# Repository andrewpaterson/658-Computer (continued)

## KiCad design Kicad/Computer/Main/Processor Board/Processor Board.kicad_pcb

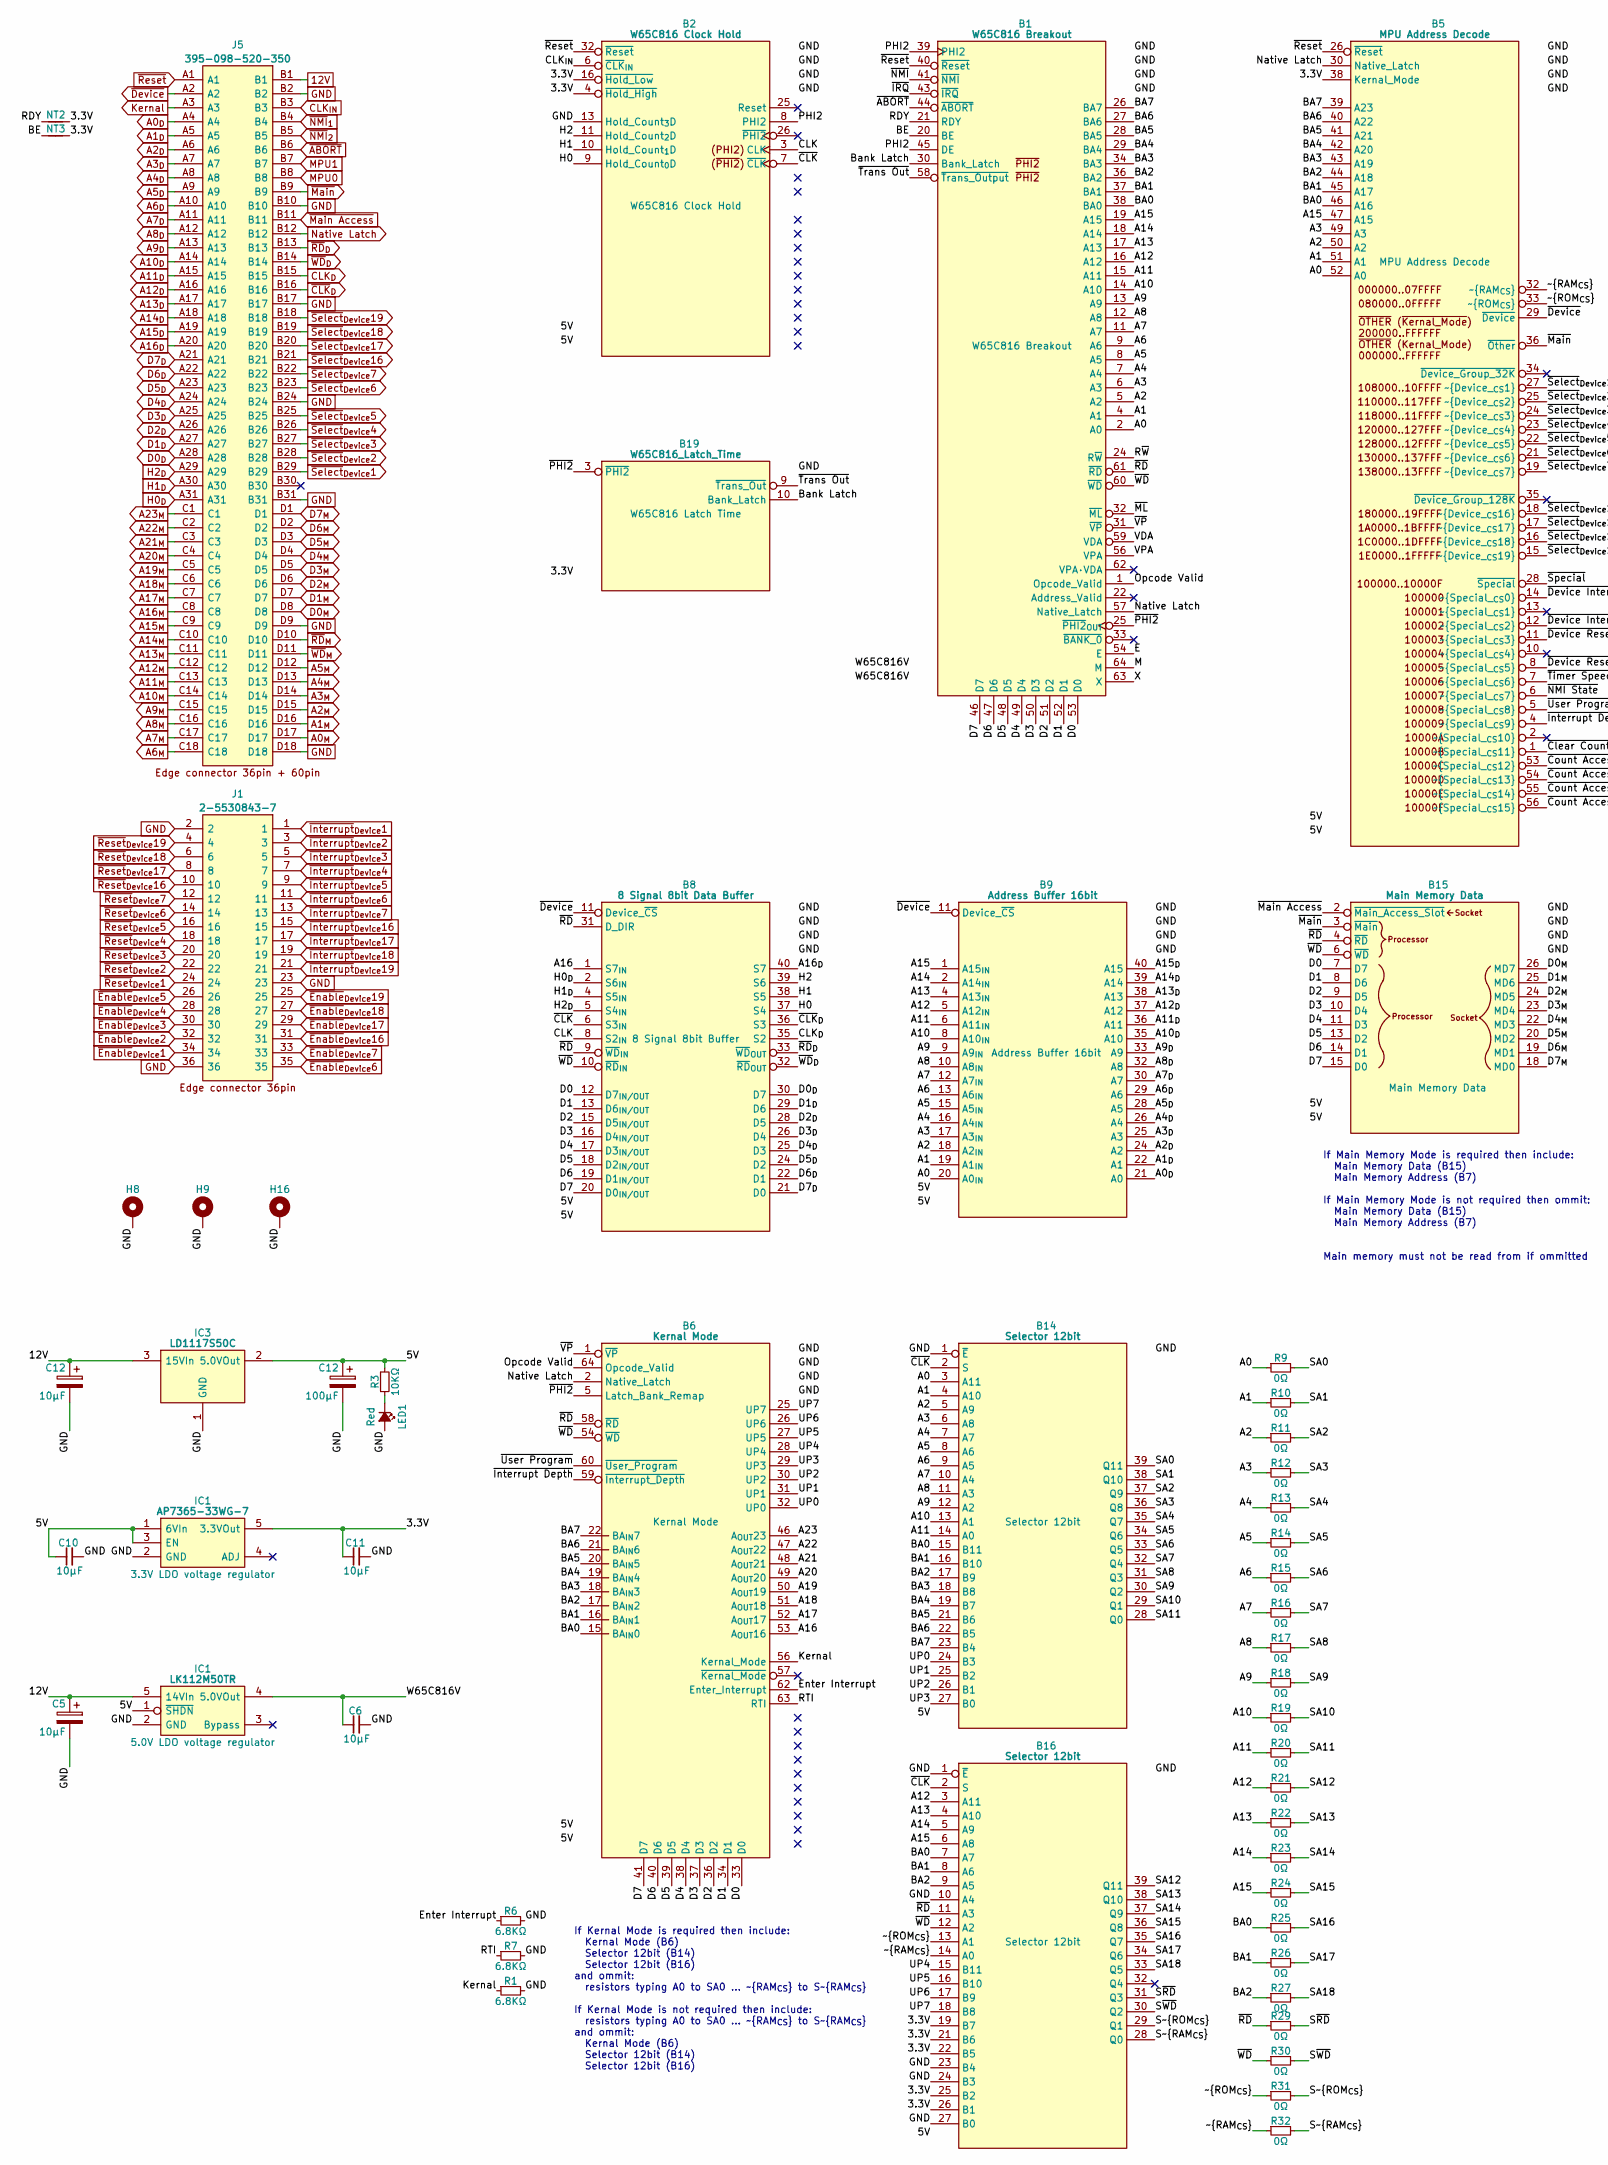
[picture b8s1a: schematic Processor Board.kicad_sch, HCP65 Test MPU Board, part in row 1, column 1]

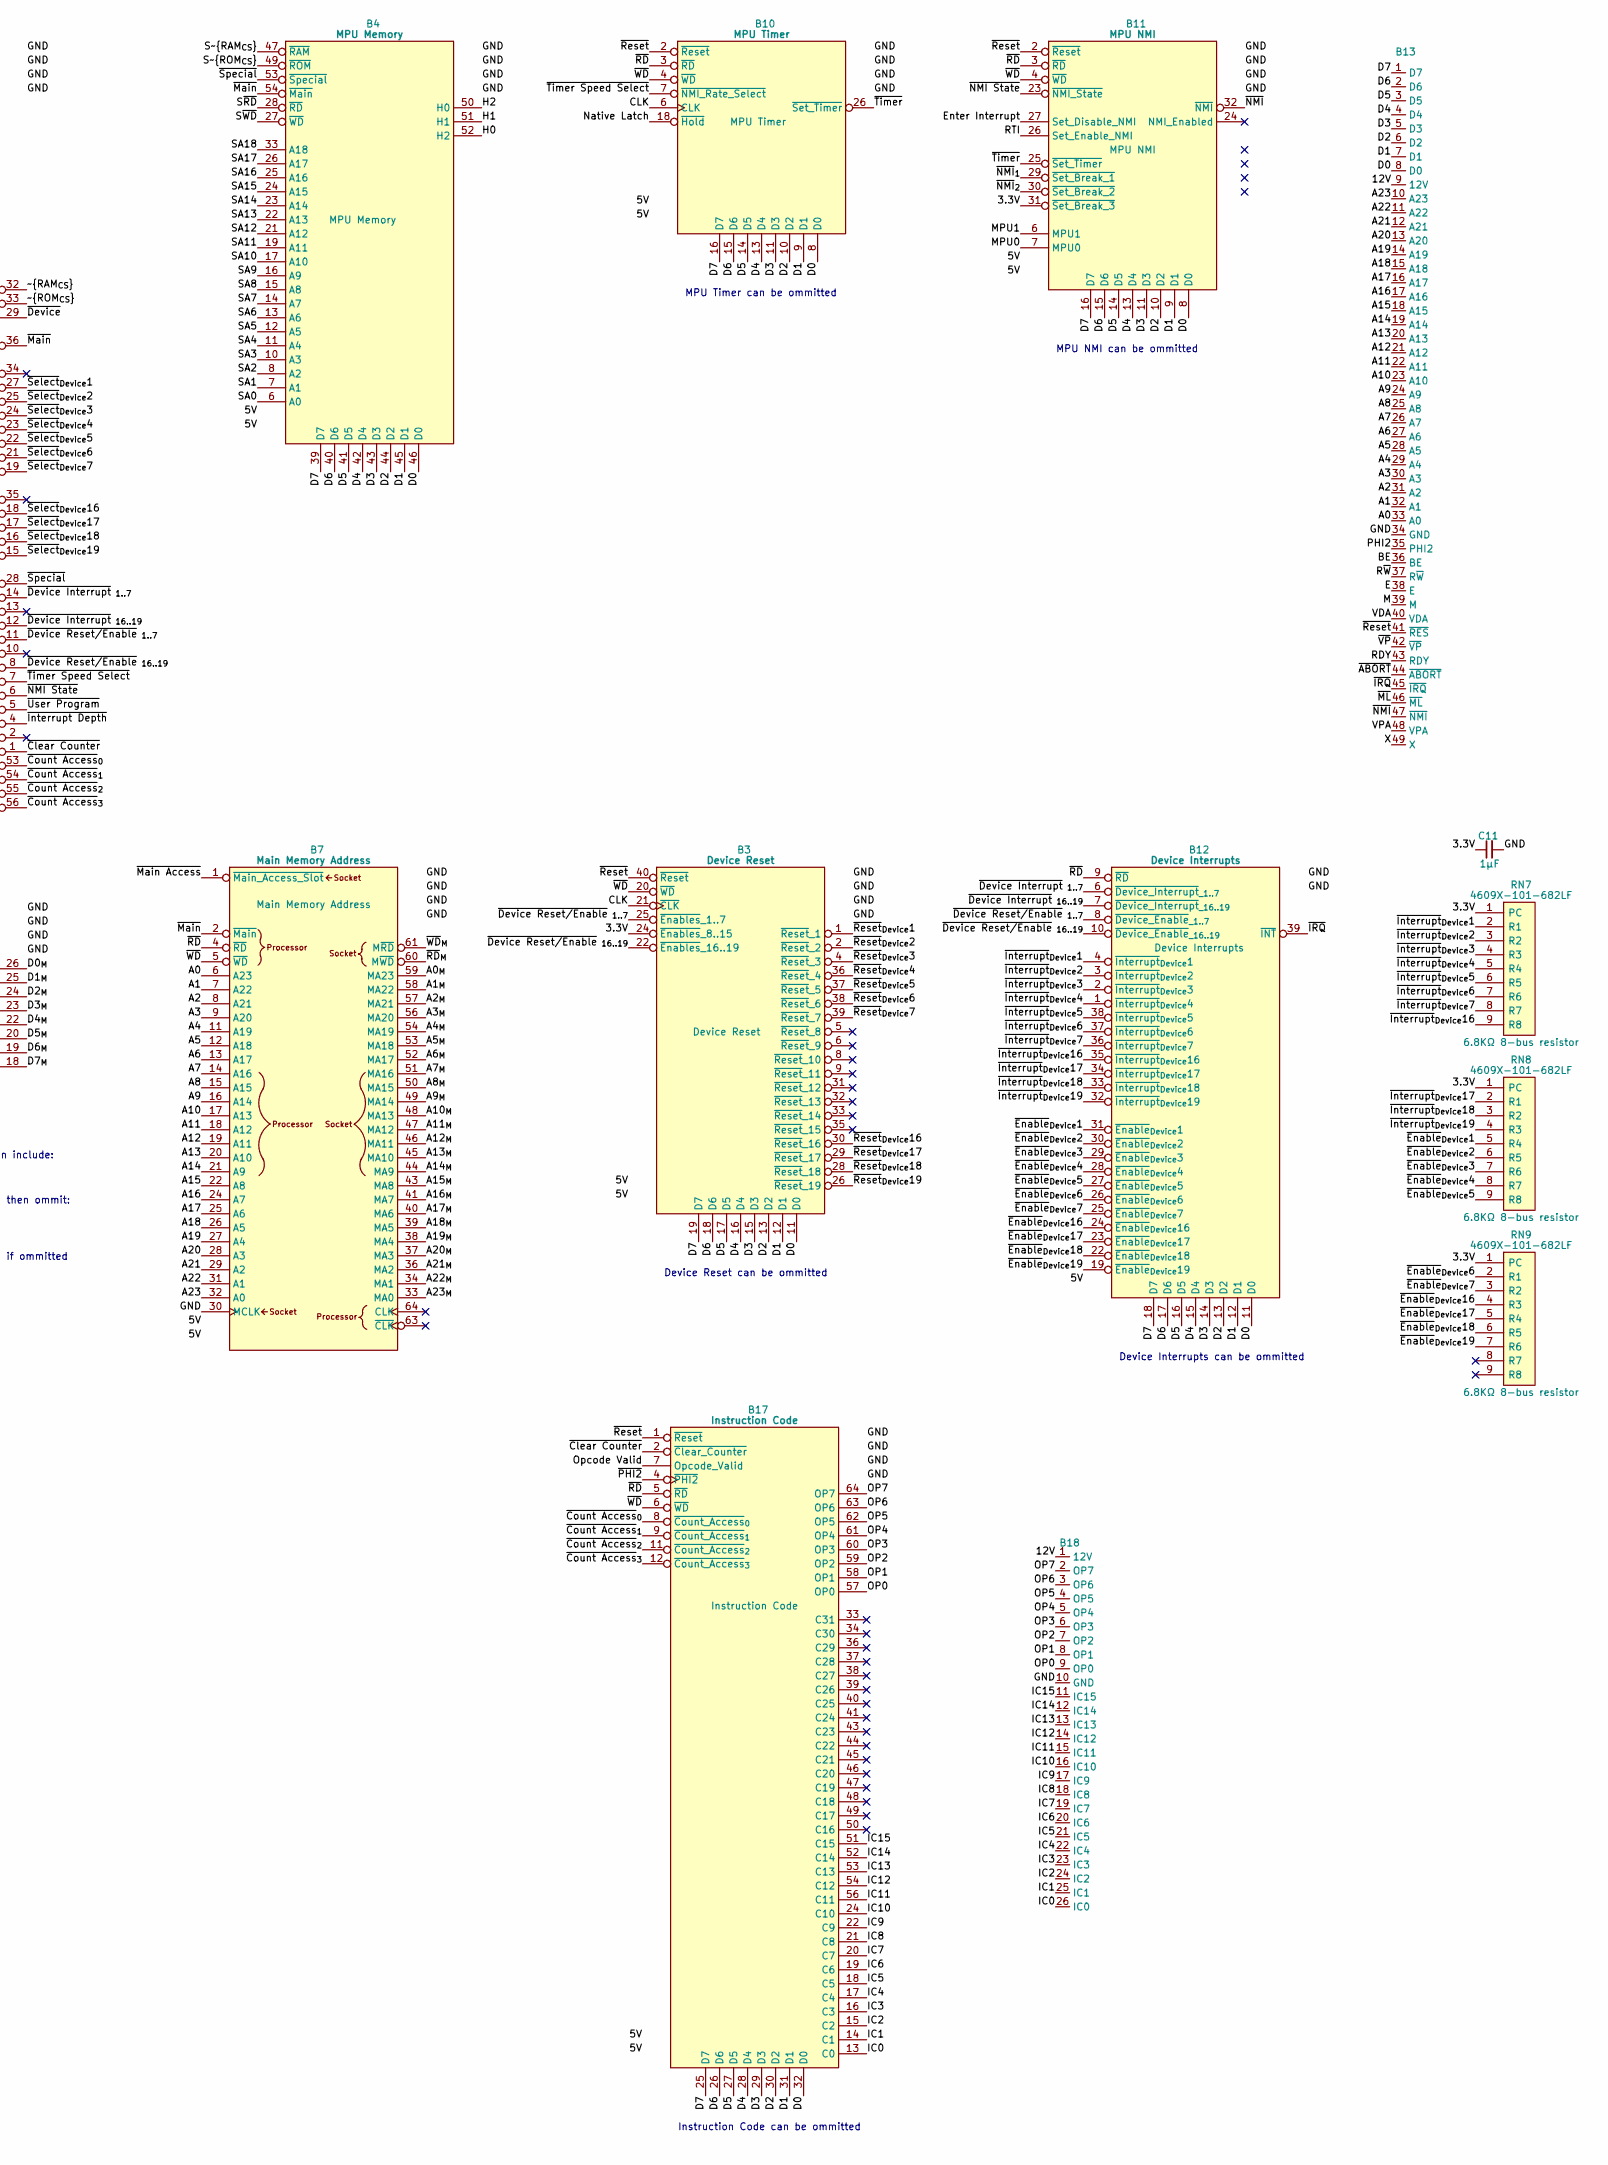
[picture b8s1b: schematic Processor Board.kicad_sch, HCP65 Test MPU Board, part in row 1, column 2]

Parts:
B1: W65C816 Breakout; HCP65_W65C816_Breakout
B2: W65C816 Clock Hold; HCP65_W65C816_Clock_Hold
B3: Device Reset; HCP65_Device_Reset
B4: MPU Memory; HCP65_MPU_Memory
B5: MPU Address Decode; HCP65_MPU_Address_Decode
B6: Kernal Mode; HCP65_Kernal_Mode
B7: Main Memory Address; HCP65_Main_Memory_Address
B8: 8 Signal 8bit Data Buffer; HCP65_Data_and_Signal_Buffer
B9: Address Buffer 16bit; HCP65_Address_Buffer_16bit
B10: MPU Timer; HCP65_MPU_Timer
B11: MPU NMI; HCP65_MPU_NMI
B12: Device Interrupts; HCP65_Device_Interrupts
B13: HCP65_W65C816_Debug_Display
B14, B16: Selector 12bit; HCP65_Selector_12bit
B15: Main Memory Data; HCP65_Main_Memory_Data
B17: Instruction Code; HCP65_Instruction_Code
B18: HCP65_W65C816_Debug_Instruction
B19: W65C816_Latch_Time; HCP65_W65C816_Latch_Time
C5: 10μF; CP_Radial_D4.0mm_P2.00mm
C6, C10: 10µF; C_0805
C11: 1μF; C_0805
C12: 100μF; CP_Radial_D4.0mm_P2.00mm
H8, H9, H16: MountingHole_Pad; HCP65_MountingHole_M3_
IC1: AP7365-33WG-7; SOT95P285X130-5N; Manufacturer_Part_Number AP7365-33WG-7; Mouser Part Number 621-AP7365-33WG-7
IC3: LD1117S50C; LD1117S33C; Manufacturer_Part_Number LD1117S50C
J1: 2-5530843-7; 36pin Edge Connector; Manufacturer_Part_Number 2-5530843-7; Mouser Part Number 571-2-5530843-7
J5: 395-098-520-350; 98pin Edge Connector; Manufacturer_Part_Number 395-098-520-350; Mouser Part Number 587-395-098-520-350
LED1: Red; LED_D5.0mm
NT2, NT3: NetTie; NetTie-2_SMD_Pad0.5mm
R1, R6, R7: 6.8KΩ; R_0805
R3: 10KΩ; R_0805
R9, R10, R11, R12, R13, R14, R15, R16, R17, R18, R19, R20, R21, R22, R23, R24, R25, R26, R27, R29, R30, R31, R32: 0Ω; R_0805
RN7, RN8, RN9: 4609X-101-682LF; 4609X; Manufacturer_Part_Number 4609X-101-682LF; Mouser Part Number 652-4609X-1LF-6.8K

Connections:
/A0: B1.2 (A0), B5.52 (A0), B7.6 (A23), B9.20 (A0_{IN}), B13.33 (A0), B14.3 (A11), R9.1
/A1: B1.4 (A1), B5.51 (A1), B7.7 (A22), B9.19 (A1_{IN}), B13.32 (A1), B14.4 (A10), R10.1
/A2: B1.5 (A2), B5.50 (A2), B7.8 (A21), B9.18 (A2_{IN}), B13.31 (A2), B14.5 (A9), R11.1
/A3: B1.6 (A3), B5.49 (A3), B7.9 (A20), B9.17 (A3_{IN}), B13.30 (A3), B14.6 (A8), R12.1
/A4: B1.7 (A4), B7.11 (A19), B9.16 (A4_{IN}), B13.29 (A4), B14.7 (A7), R13.1
/A5: B1.8 (A5), B7.12 (A18), B9.15 (A5_{IN}), B13.28 (A5), B14.8 (A6), R14.1
/A6: B1.9 (A6), B7.13 (A17), B9.13 (A6_{IN}), B13.27 (A6), B14.9 (A5), R15.1
/A7: B1.11 (A7), B7.14 (A16), B9.12 (A7_{IN}), B13.26 (A7), B14.10 (A4), R16.1
/A8: B1.12 (A8), B7.15 (A15), B9.10 (A8_{IN}), B13.25 (A8), B14.11 (A3), R17.1
/A9: B1.13 (A9), B7.16 (A14), B9.9 (A9_{IN}), B13.24 (A9), B14.12 (A2), R18.1
/A10: B1.14 (A10), B7.17 (A13), B9.8 (A10_{IN}), B13.23 (A10), B14.13 (A1), R19.1
/A11: B1.15 (A11), B7.18 (A12), B9.6 (A11_{IN}), B13.22 (A11), B14.14 (A0), R20.1
/A12: B1.16 (A12), B7.19 (A11), B9.5 (A12_{IN}), B13.21 (A12), B16.3 (A11), R21.1
/A13: B1.17 (A13), B7.20 (A10), B9.4 (A13_{IN}), B13.20 (A13), B16.4 (A10), R22.1
/A14: B1.18 (A14), B7.21 (A9), B9.2 (A14_{IN}), B13.19 (A14), B16.5 (A9), R23.1
/A15: B1.19 (A15), B5.47 (A15), B7.22 (A8), B9.1 (A15_{IN}), B13.18 (A15), B16.6 (A8), R24.1
/A16: B6.53 (A_{OUT}16), B7.24 (A7), B8.1 (S7_{IN}), B13.17 (A16)
/A17: B6.52 (A_{OUT}17), B7.25 (A6), B13.16 (A17)
/A18: B6.51 (A_{OUT}18), B7.26 (A5), B13.15 (A18)
/A19: B6.50 (A_{OUT}19), B7.27 (A4), B13.14 (A19)
/A20: B6.49 (A_{OUT}20), B7.28 (A3), B13.13 (A20)
/A21: B6.48 (A_{OUT}21), B7.29 (A2), B13.12 (A21)
/A22: B6.47 (A_{OUT}22), B7.31 (A1), B13.11 (A22)
/A23: B6.46 (A_{OUT}23), B7.32 (A0), B13.10 (A23)
/BA0: B1.38 (BA0), B5.46 (A16), B6.15 (BA_{IN}0), B14.15 (B11), B16.7 (A7), R25.1
/BA1: B1.37 (BA1), B5.45 (A17), B6.16 (BA_{IN}1), B14.16 (B10), B16.8 (A6), R26.1
/BA2: B1.36 (BA2), B5.44 (A18), B6.17 (BA_{IN}2), B14.17 (B9), B16.9 (A5), R27.1
/BA3: B1.34 (BA3), B5.43 (A19), B6.18 (BA_{IN}3), B14.18 (B8)
/BA4: B1.29 (BA4), B5.42 (A20), B6.19 (BA_{IN}4), B14.19 (B7)
/BA5: B1.28 (BA5), B5.41 (A21), B6.20 (BA_{IN}5), B14.21 (B6)
/BA6: B1.27 (BA6), B5.40 (A22), B6.21 (BA_{IN}6), B14.22 (B5)
/BA7: B1.26 (BA7), B5.39 (A23), B6.22 (BA_{IN}7), B14.23 (B4)
/BE: B1.20 (BE), B13.36 (BE), NT3.1
/Bank Latch: B1.30 (Bank_Latch), B19.10 (Bank_Latch)
/CLK: B2.3 (CLK), B3.21 (~CLK), B8.8 (S2_{IN}), B10.6 (CLK)
/D0: B1.53 (D0), B3.11 (D0), B4.46 (D0), B6.33 (D0), B8.12 (D7_{IN/OUT}), B10.8 (D0), B11.8 (D0), B12.11 (D0), B13.8 (D0), B15.7 (D7), B17.32 (D0)
/D1: B1.52 (D1), B3.12 (D1), B4.45 (D1), B6.34 (D1), B8.13 (D6_{IN/OUT}), B10.9 (D1), B11.9 (D1), B12.12 (D1), B13.7 (D1), B15.8 (D6), B17.31 (D1)
/D2: B1.51 (D2), B3.13 (D2), B4.44 (D2), B6.36 (D2), B8.15 (D5_{IN/OUT}), B10.10 (D2), B11.10 (D2), B12.13 (D2), B13.6 (D2), B15.9 (D5), B17.30 (D2)
/D3: B1.50 (D3), B3.15 (D3), B4.43 (D3), B6.37 (D3), B8.16 (D4_{IN/OUT}), B10.11 (D3), B11.11 (D3), B12.14 (D3), B13.5 (D3), B15.10 (D4), B17.29 (D3)
/D4: B1.49 (D4), B3.16 (D4), B4.42 (D4), B6.38 (D4), B8.17 (D3_{IN/OUT}), B10.13 (D4), B11.13 (D4), B12.15 (D4), B13.4 (D4), B15.11 (D3), B17.28 (D4)
/D5: B1.48 (D5), B3.17 (D5), B4.41 (D5), B6.39 (D5), B8.18 (D2_{IN/OUT}), B10.14 (D5), B11.14 (D5), B12.16 (D5), B13.3 (D5), B15.13 (D2), B17.27 (D5)
/D6: B1.47 (D6), B3.18 (D6), B4.40 (D6), B6.40 (D6), B8.19 (D1_{IN/OUT}), B10.15 (D6), B11.15 (D6), B12.17 (D6), B13.2 (D6), B15.14 (D1), B17.26 (D6)
/D7: B1.46 (D7), B3.19 (D7), B4.39 (D7), B6.41 (D7), B8.20 (D0_{IN/OUT}), B10.16 (D7), B11.16 (D7), B12.18 (D7), B13.1 (D7), B15.15 (D0), B17.25 (D7)
/E: B1.54 (E), B13.38 (E)
/Enter Interrupt: B6.62 (Enter_Interrupt), B11.27 (Set_Disable_NMI), R6.1
/H0: B2.9 (Hold_Count_{0}D), B4.52 (H2), B8.37 (S4)
/H1: B2.10 (Hold_Count_{1}D), B4.51 (H1), B8.38 (S5)
/H2: B2.11 (Hold_Count_{2}D), B4.50 (H0), B8.39 (S6)
/IC0: B17.13 (C0), B18.26 (IC0)
/IC1: B17.14 (C1), B18.25 (IC1)
/IC2: B17.15 (C2), B18.24 (IC2)
/IC3: B17.16 (C3), B18.23 (IC3)
/IC4: B17.17 (C4), B18.22 (IC4)
/IC5: B17.18 (C5), B18.21 (IC5)
/IC6: B17.19 (C6), B18.20 (IC6)
/IC7: B17.20 (C7), B18.19 (IC7)
/IC8: B17.21 (C8), B18.18 (IC8)
/IC9: B17.22 (C9), B18.17 (IC9)
/IC10: B17.24 (C10), B18.16 (IC10)
/IC11: B17.56 (C11), B18.15 (IC11)
/IC12: B17.54 (C12), B18.14 (IC12)
/IC13: B17.53 (C13), B18.13 (IC13)
/IC14: B17.52 (C14), B18.12 (IC14)
/IC15: B17.51 (C15), B18.11 (IC15)
/M: B1.64 (M), B13.39 (M)
/OP0: B17.57 (OP0), B18.9 (OP0)
/OP1: B17.58 (OP1), B18.8 (OP1)
/OP2: B17.59 (OP2), B18.7 (OP2)
/OP3: B17.60 (OP3), B18.6 (OP3)
/OP4: B17.61 (OP4), B18.5 (OP4)
/OP5: B17.62 (OP5), B18.4 (OP5)
/OP6: B17.63 (OP6), B18.3 (OP6)
/OP7: B17.64 (OP7), B18.2 (OP7)
/Opcode Valid: B1.1 (Opcode_Valid), B6.64 (Opcode_Valid), B17.7 (Opcode_Valid)
/PHI2: B1.39 (PHI2), B1.45 (DE), B2.8 (PHI2), B13.35 (PHI2)
/RDY: B1.21 (RDY), B13.43 (RDY), NT2.1
/RTI: B6.63 (RTI), B11.26 (Set_Enable_NMI), R7.1
/R~W: B1.24 (R~W), B13.37 (R~W)
/SA0: B4.6 (A0), B14.39 (Q11), R9.2
/SA1: B4.7 (A1), B14.38 (Q10), R10.2
/SA2: B4.8 (A2), B14.37 (Q9), R11.2
/SA3: B4.10 (A3), B14.36 (Q8), R12.2
/SA4: B4.11 (A4), B14.35 (Q7), R13.2
/SA5: B4.12 (A5), B14.34 (Q6), R14.2
/SA6: B4.13 (A6), B14.33 (Q5), R15.2
/SA7: B4.14 (A7), B14.32 (Q4), R16.2
/SA8: B4.15 (A8), B14.31 (Q3), R17.2
/SA9: B4.16 (A9), B14.30 (Q2), R18.2
/SA10: B4.17 (A10), B14.29 (Q1), R19.2
/SA11: B4.19 (A11), B14.28 (Q0), R20.2
/SA12: B4.21 (A12), B16.39 (Q11), R21.2
/SA13: B4.22 (A13), B16.38 (Q10), R22.2
/SA14: B4.23 (A14), B16.37 (Q9), R23.2
/SA15: B4.24 (A15), B16.36 (Q8), R24.2
/SA16: B4.25 (A16), B16.35 (Q7), R25.2
/SA17: B4.26 (A17), B16.34 (Q6), R26.2
/SA18: B4.33 (A18), B16.33 (Q5), R27.2
/S~RAM_{CS}: B4.47 (~RAM), B16.28 (Q0), R32.2
/S~RD: B4.28 (~RD), B16.31 (Q3), R29.2
/S~ROM_{CS}: B4.49 (~ROM), B16.29 (Q1), R31.2
/S~WD: B4.27 (~WD), B16.30 (Q2), R30.2
/UP0: B6.32 (UP0), B14.24 (B3)
/UP1: B6.31 (UP1), B14.25 (B2)
/UP2: B6.30 (UP2), B14.26 (B1)
/UP3: B6.29 (UP3), B14.27 (B0)
/UP4: B6.28 (UP4), B16.15 (B11)
/UP5: B6.27 (UP5), B16.16 (B10)
/UP6: B6.26 (UP6), B16.17 (B9)
/UP7: B6.25 (UP7), B16.18 (B8)
/VDA: B1.59 (VDA), B13.40 (VDA)
/VPA: B1.56 (VPA), B13.48 (VPA)
/W65C816V: B1.3 (5V), B1.35 (5V), C6.1, IC1.4 (5.0VOut)
/X: B1.63 (X), B13.49 (X)
/~CLK: B2.7 (~CLK), B8.6 (S3_{IN}), B14.2 (S), B16.2 (S)
/~Clear Counter: B5.1 (~Special__{CS11}), B17.2 (~Clear_Counter)
/~Count Access_{0}: B5.53 (~Special__{CS12}), B17.8 (~Count_Access_{0})
/~Count Access_{1}: B5.54 (~Special__{CS13}), B17.9 (~Count_Access_{1})
/~Count Access_{2}: B5.55 (~Special__{CS14}), B17.11 (~Count_Access_{2})
/~Count Access_{3}: B5.56 (~Special__{CS15}), B17.12 (~Count_Access_{3})
/~Device Interrupt_{ 1..7}: B5.14 (~Special__{CS0}), B12.6 (~Device_Interrupt_{_1..7})
/~Device Interrupt_{ 16..19}: B5.12 (~Special__{CS2}), B12.7 (~Device_Interrupt_{_16..19})
/~Device Reset/Enable_{ 1..7}: B3.25 (~Enables_1..7), B5.11 (~Special__{CS3}), B12.8 (~Device_Enable_{_1..7})
/~Device Reset/Enable_{ 16..19}: B3.22 (~Enables_16..19), B5.8 (~Special__{CS5}), B12.10 (~Device_Enable_{_16..19})
/~IRQ: B1.43 (~IRQ), B12.39 (~INT), B13.45 (~IRQ)
/~Interrupt Depth: B5.4 (~Special__{CS9}), B6.59 (~Interrupt_Depth)
/~ML: B1.32 (~ML), B13.46 (~ML)
/~NMI State: B5.6 (~Special__{CS7}), B11.23 (~NMI_State)
/~NMI: B1.41 (~NMI), B11.32 (~NMI), B13.47 (~NMI)
/~PHI2: B1.25 (~PHI2_{OUT}), B6.5 (Latch_Bank_Remap), B17.4 (~PHI2), B19.3 (~PHI2)
/~RAM_{CS}: B5.32 (~RAM_{CS}), B16.14 (A0), R32.1
/~RD: B1.61 (~RD), B6.58 (~RD), B7.4 (~RD), B8.9 (~WD_{IN}), B8.31 (D_DIR), B10.3 (~RD), B11.3 (~RD), B12.9 (~RD), B15.4 (~RD), B16.11 (A3), B17.5 (~RD), R29.1
/~ROM_{CS}: B5.33 (~ROM_{CS}), B16.13 (A1), R31.1
/~Special: B4.53 (~Special), B5.28 (~Special)
/~Timer Speed Select: B5.7 (~Special__{CS6}), B10.7 (~NMI_Rate_Select)
/~Timer: B10.26 (~Set_Timer), B11.25 (~Set_Timer)
/~Trans Out: B1.58 (~Trans_Output), B19.9 (~Trans_Out)
/~User Program: B5.5 (~Special__{CS8}), B6.60 (~User_Program)
/~VP: B1.31 (~VP), B6.1 (~VP), B13.42 (~VP)
/~WD: B1.60 (~WD), B3.20 (~WD), B6.54 (~WD), B7.5 (~WD), B8.10 (~RD_{IN}), B10.4 (~WD), B11.4 (~WD), B15.6 (~WD), B16.12 (A2), B17.6 (~WD), R30.1
A0_{D}: B9.21 (A0), J5.A4
A0_{M}: B7.59 (MA23), J5.D17
A1_{D}: B9.22 (A1), J5.A5
A1_{M}: B7.58 (MA22), J5.D16
A2_{D}: B9.24 (A2), J5.A6
A2_{M}: B7.57 (MA21), J5.D15
A3_{D}: B9.25 (A3), J5.A7
A3_{M}: B7.56 (MA20), J5.D14
A4_{D}: B9.26 (A4), J5.A8
A4_{M}: B7.54 (MA19), J5.D13
A5_{D}: B9.28 (A5), J5.A9
A5_{M}: B7.53 (MA18), J5.D12
A6_{D}: B9.29 (A6), J5.A10
A6_{M}: B7.52 (MA17), J5.C18
A7_{D}: B9.30 (A7), J5.A11
A7_{M}: B7.51 (MA16), J5.C17
A8_{D}: B9.32 (A8), J5.A12
A8_{M}: B7.50 (MA15), J5.C16
A9_{D}: B9.33 (A9), J5.A13
A9_{M}: B7.49 (MA14), J5.C15
A10_{D}: B9.35 (A10), J5.A14
A10_{M}: B7.48 (MA13), J5.C14
A11_{D}: B9.36 (A11), J5.A15
A11_{M}: B7.47 (MA12), J5.C13
A12_{D}: B9.37 (A12), J5.A16
A12_{M}: B7.46 (MA11), J5.C12
A13_{D}: B9.38 (A13), J5.A17
A13_{M}: B7.45 (MA10), J5.C11
A14_{D}: B9.39 (A14), J5.A18
A14_{M}: B7.44 (MA9), J5.C10
A15_{D}: B9.40 (A15), J5.A19
A15_{M}: B7.43 (MA8), J5.C9
A16_{D}: B8.40 (S7), J5.A20
A16_{M}: B7.41 (MA7), J5.C8
A17_{M}: B7.40 (MA6), J5.C7
A18_{M}: B7.39 (MA5), J5.C6
A19_{M}: B7.38 (MA4), J5.C5
A20_{M}: B7.37 (MA3), J5.C4
A21_{M}: B7.36 (MA2), J5.C3
A22_{M}: B7.34 (MA1), J5.C2
A23_{M}: B7.33 (MA0), J5.C1
CLK_{D}: B8.35 (S2), J5.B15
CLK_{IN}: B2.6 (~CLK_{IN}), J5.B3
D0_{D}: B8.30 (D7), J5.A28
D0_{M}: B15.26 (MD7), J5.D8
D1_{D}: B8.29 (D6), J5.A27
D1_{M}: B15.25 (MD6), J5.D7
D2_{D}: B8.28 (D5), J5.A26
D2_{M}: B15.24 (MD5), J5.D6
D3_{D}: B8.26 (D4), J5.A25
D3_{M}: B15.23 (MD4), J5.D5
D4_{D}: B8.25 (D3), J5.A24
D4_{M}: B15.22 (MD3), J5.D4
D5_{D}: B8.24 (D2), J5.A23
D5_{M}: B15.20 (MD2), J5.D3
D6_{D}: B8.22 (D1), J5.A22
D6_{M}: B15.19 (MD1), J5.D2
D7_{D}: B8.21 (D0), J5.A21
D7_{M}: B15.18 (MD0), J5.D1
GND: B1.10 (GND), B1.23 (GND), B1.42 (GND), B1.55 (GND), B2.5 (GND), B2.12 (GND), B2.13 (Hold_Count_{3}D), B2.21 (GND), B2.28 (GND), B3.7 (GND), B3.14 (GND), B3.27 (GND), B3.34 (GND), B4.9 (GND), B4.20 (GND), B4.37 (GND), B4.48 (GND), B5.9 (GND), B5.20 (GND), B5.37 (GND), B5.48 (GND), B6.10 (GND), B6.23 (GND), B6.42 (GND), B6.55 (GND), B7.10 (GND), B7.23 (GND), B7.30 (MCLK), B7.42 (GND), B7.55 (GND), B8.7 (GND), B8.14 (GND), B8.27 (GND), B8.34 (GND), B9.7 (GND), B9.14 (GND), B9.27 (GND), B9.34 (GND), B10.5 (GND), B10.12 (GND), B10.21 (GND), B10.28 (GND), B11.5 (GND), B11.12 (GND), B11.21 (GND), B11.28 (GND), B12.21 (GND), B12.40 (GND), B13.34 (GND), B14.1 (~E), B14.40 (GND), B15.5 (GND), B15.12 (GND), B15.21 (GND), B15.28 (GND), B16.1 (~E), B16.10 (A4), B16.23 (B4), B16.24 (B3), B16.27 (B0), B16.40 (GND), B17.10 (GND), B17.23 (GND), B17.42 (GND), B17.55 (GND), B18.10 (GND), B19.12 (GND), C5.2, C6.2, C11.2, H8.1 (GND), H9.1 (GND), H16.1 (GND), IC1.2 (GND), IC3.1 (GND), J1.2, J1.23, J1.36, J5.B2, J5.B10, J5.B17, J5.B24, J5.B31, J5.D9, J5.D18, R1.2, R6.2, R7.2; also elsewhere on the board
H0_{D}: B8.2 (S6_{IN}), J5.A31
H1_{D}: B8.4 (S5_{IN}), J5.A30
H2_{D}: B8.5 (S4_{IN}), J5.A29
Kernal: B6.56 (Kernal_Mode), J5.A3, R1.1
MPU0: B11.7 (MPU0), J5.B8
MPU1: B11.6 (MPU1), J5.B7
Native Latch: B1.57 (Native_Latch), B5.30 (Native_Latch), B6.2 (Native_Latch), B10.18 (~Hold), J5.B12
unnamed 206: R3.1; also elsewhere on the board
~ABORT: B1.44 (~ABORT), B13.44 (~ABORT), J5.B6
~CLK_{D}: B8.36 (S3), J5.B16
~Device: B5.29 (~Device), B8.11 (Device_~CS), B9.11 (Device_~CS), J5.A2
~Enable_{Device}1: B12.31 (~Enable_{Device}1), J1.34, RN8.5 (R4)
~Enable_{Device}2: B12.30 (~Enable_{Device}2), J1.32, RN8.6 (R5)
~Enable_{Device}3: B12.29 (~Enable_{Device}3), J1.30, RN8.7 (R6)
~Enable_{Device}4: B12.28 (~Enable_{Device}4), J1.28, RN8.8 (R7)
~Enable_{Device}5: B12.27 (~Enable_{Device}5), J1.26, RN8.9 (R8)
~Enable_{Device}6: B12.26 (~Enable_{Device}6), J1.35, RN9.2 (R1)
~Enable_{Device}7: B12.25 (~Enable_{Device}7), J1.33, RN9.3 (R2)
~Enable_{Device}16: B12.24 (~Enable_{Device}16), J1.31, RN9.4 (R3)
~Enable_{Device}17: B12.23 (~Enable_{Device}17), J1.29, RN9.5 (R4)
~Enable_{Device}18: B12.22 (~Enable_{Device}18), J1.27, RN9.6 (R5)
~Enable_{Device}19: B12.19 (~Enable_{Device}19), J1.25, RN9.7 (R6)
~Interrupt_{Device}1: B12.4 (~Interrupt_{Device}1), J1.1, RN7.2 (R1)
~Interrupt_{Device}2: B12.3 (~Interrupt_{Device}2), J1.3, RN7.3 (R2)
~Interrupt_{Device}3: B12.2 (~Interrupt_{Device}3), J1.5, RN7.4 (R3)
~Interrupt_{Device}4: B12.1 (~Interrupt_{Device}4), J1.7, RN7.5 (R4)
~Interrupt_{Device}5: B12.38 (~Interrupt_{Device}5), J1.9, RN7.6 (R5)
~Interrupt_{Device}6: B12.37 (~Interrupt_{Device}6), J1.11, RN7.7 (R6)
~Interrupt_{Device}7: B12.36 (~Interrupt_{Device}7), J1.13, RN7.8 (R7)
~Interrupt_{Device}16: B12.35 (~Interrupt_{Device}16), J1.15, RN7.9 (R8)
~Interrupt_{Device}17: B12.34 (~Interrupt_{Device}17), J1.17, RN8.2 (R1)
~Interrupt_{Device}18: B12.33 (~Interrupt_{Device}18), J1.19, RN8.3 (R2)
~Interrupt_{Device}19: B12.32 (~Interrupt_{Device}19), J1.21, RN8.4 (R3)
~Main Access: B7.1 (~Main_Access_Slot), B15.2 (~Main_Access_Slot), J5.B11
~Main: B4.54 (~Main), B5.36 (~Other), B7.2 (~Main), B15.3 (~Main), J5.B9
~NMI_{1}: B11.29 (~Set_Break_1), J5.B4
~NMI_{2}: B11.30 (~Set_Break_2), J5.B5
~RD_{D}: B8.33 (~WD_{OUT}), J5.B13
~RD_{M}: B7.60 (M~WD), J5.D10
~Reset: B1.40 (~Reset), B2.32 (~Reset), B3.40 (~Reset), B5.26 (~Reset), B10.2 (~Reset), B11.2 (~Reset), B13.41 (~RES), B17.1 (~Reset), J5.A1
~Reset_{Device}1: B3.1 (~Reset_1), J1.24
~Reset_{Device}2: B3.2 (~Reset_2), J1.22
~Reset_{Device}3: B3.4 (~Reset_3), J1.20
~Reset_{Device}4: B3.36 (~Reset_4), J1.18
~Reset_{Device}5: B3.37 (~Reset_5), J1.16
~Reset_{Device}6: B3.38 (~Reset_6), J1.14
~Reset_{Device}7: B3.39 (~Reset_7), J1.12
~Reset_{Device}16: B3.30 (~Reset_16), J1.10
~Reset_{Device}17: B3.29 (~Reset_17), J1.8
~Reset_{Device}18: B3.28 (~Reset_18), J1.6
~Reset_{Device}19: B3.26 (~Reset_19), J1.4
~Select_{Device}1: B5.27 (~Device__{CS1}), J5.B29
~Select_{Device}2: B5.25 (~Device__{CS2}), J5.B28
~Select_{Device}3: B5.24 (~Device__{CS3}), J5.B27
~Select_{Device}4: B5.23 (~Device__{CS4}), J5.B26
~Select_{Device}5: B5.22 (~Device__{CS5}), J5.B25
~Select_{Device}6: B5.21 (~Device__{CS6}), J5.B23
~Select_{Device}7: B5.19 (~Device__{CS7}), J5.B22
~Select_{Device}16: B5.18 (~Device__{CS16}), J5.B21
~Select_{Device}17: B5.17 (~Device__{CS17}), J5.B20
~Select_{Device}18: B5.16 (~Device__{CS18}), J5.B19
~Select_{Device}19: B5.15 (~Device__{CS19}), J5.B18
~WD_{D}: B8.32 (~RD_{OUT}), J5.B14
~WD_{M}: B7.61 (M~RD), J5.D11

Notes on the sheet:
If Main Memory Mode is required then include: Main Memory Data (B15) Main Memory Address (B7) If Main Memory Mode is not required then ommit: Main Memory Data (B15) Main Memory Address (B7) Main memory must not be read from if ommitted
MPU Timer can be ommitted
MPU NMI can be ommitted
Device Reset can be ommitted
Device Interrupts can be ommitted
If Kernal Mode is required then include: Kernal Mode (B6) Selector 12bit (B14) Selector 12bit (B16) and ommit: resistors typing A0 to SA0 ... ~{RAM_{CS}} to S~{RAM_{CS}} If Kernal Mode is not required then include: resistors typing A0 to SA0 ... ~{RAM_{CS}} to S~{RAM_{CS}} and ommit: Kernal Mode (B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
Instruction Code can be ommitted

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
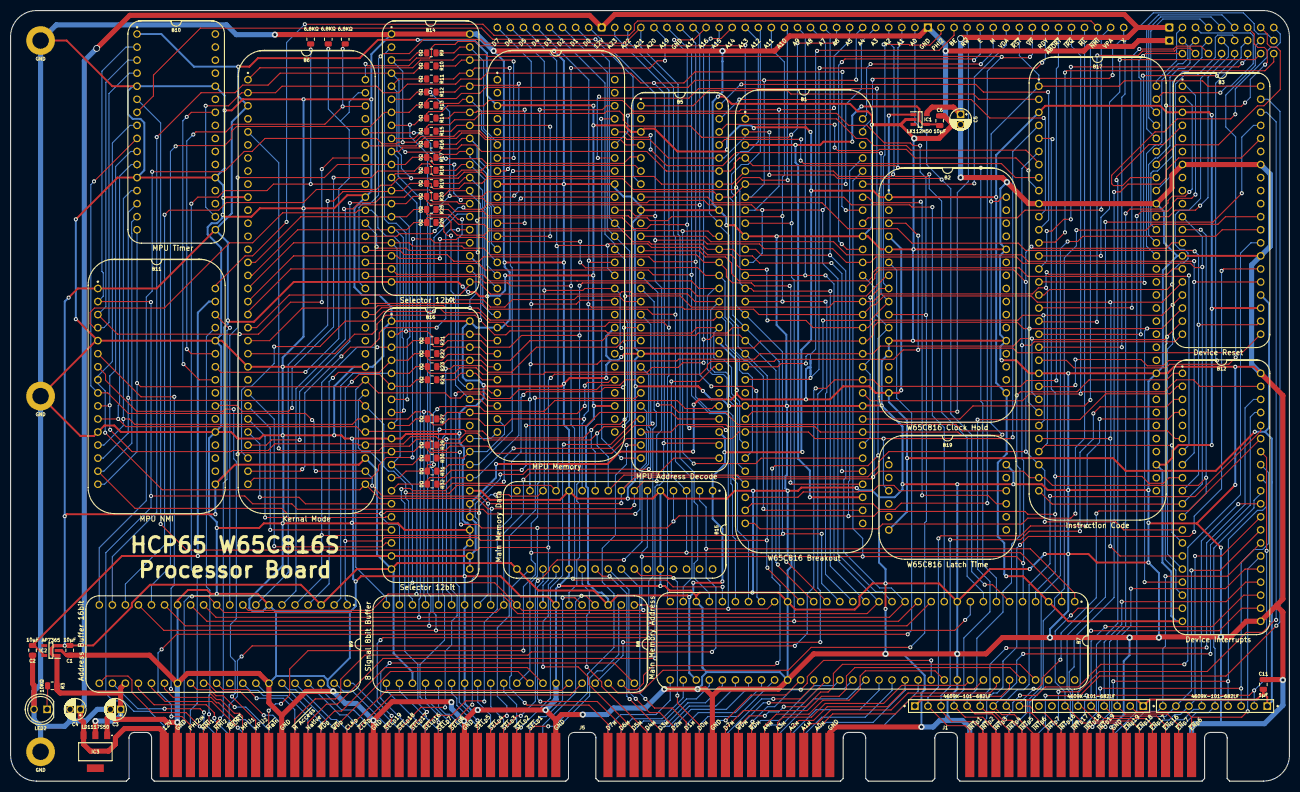
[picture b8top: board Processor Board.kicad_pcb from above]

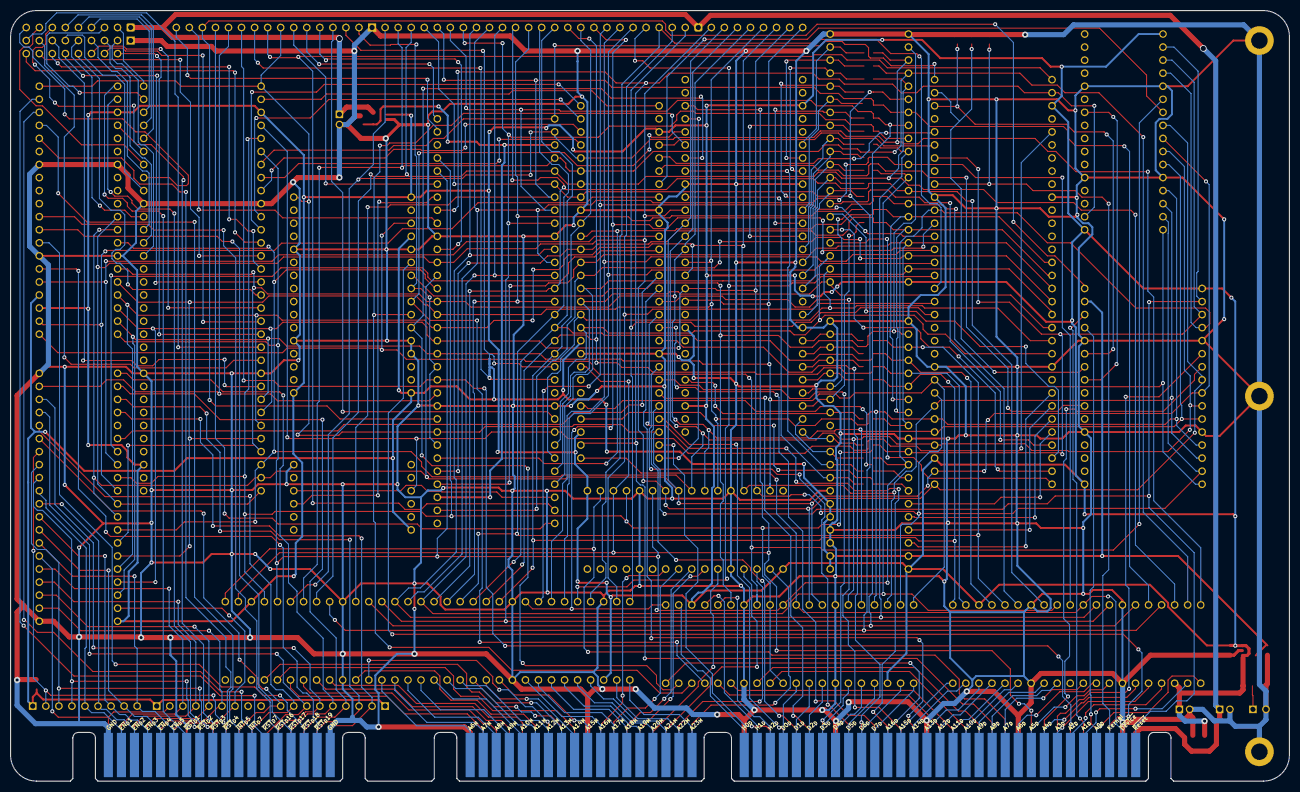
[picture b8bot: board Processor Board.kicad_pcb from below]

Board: 2 copper layers, 248.9 x 150.0 mm, 67 parts (2 on the bottom side), 266 nets.

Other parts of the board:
C1, C2: 10µF; C_0805
C3: 100μF; CP_Radial_D4.0mm_P2.00mm
C4: 10μF; CP_Radial_D4.0mm_P2.00mm
IC2: AP7365-33WG-7; SOT95P285X130-5N
LED2: Red; LED_D5.0mm

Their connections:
GND: C1.2, C2.2, C3.2, C4.2, IC2.2 (GND), LED2.2 (A); also elsewhere on the board
unnamed 206: LED2.1 (K); also elsewhere on the board
